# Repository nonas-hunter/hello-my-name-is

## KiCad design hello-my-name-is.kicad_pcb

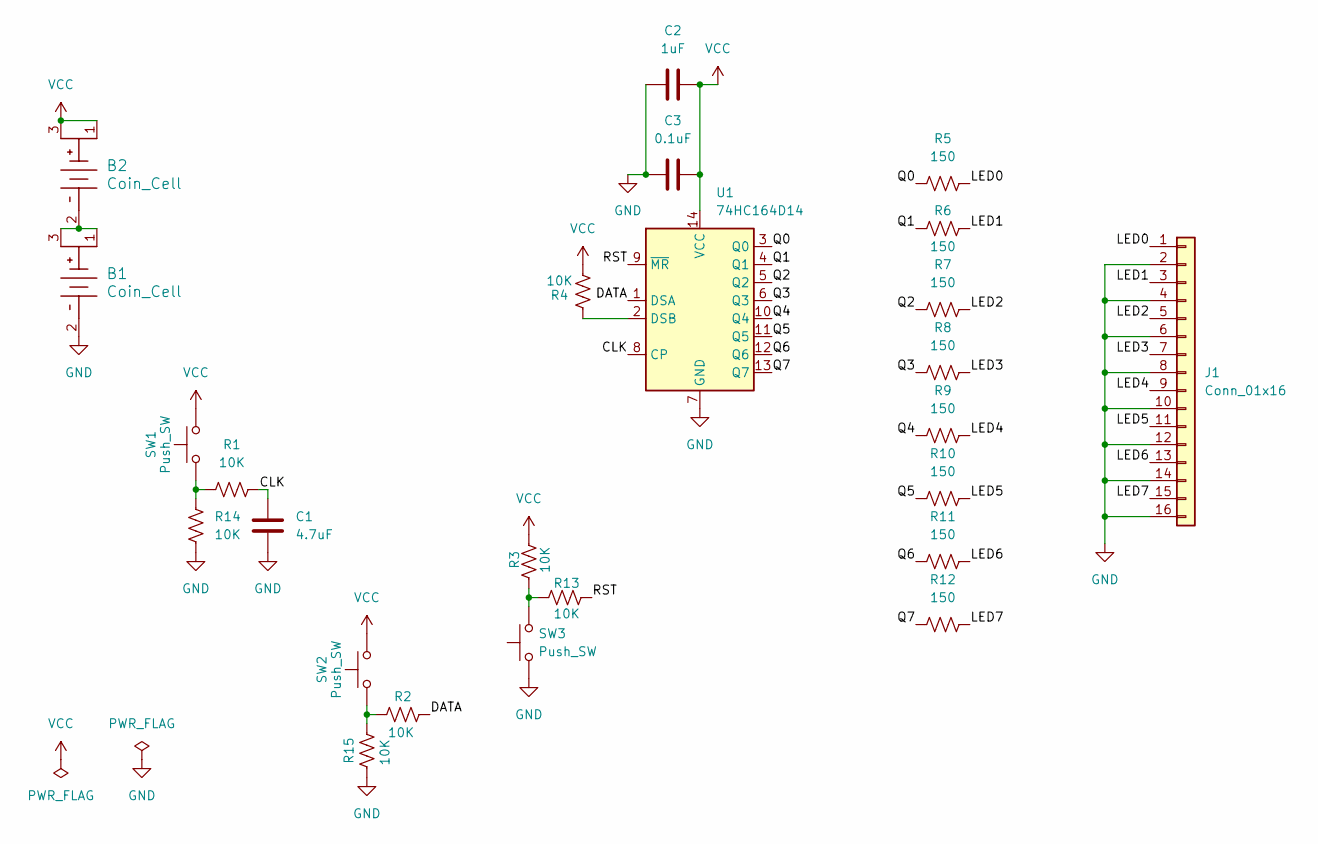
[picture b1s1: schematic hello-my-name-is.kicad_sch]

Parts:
B1, B2: Coin_Cell; BATT_HLDR_LNX; Part Number (DigiKey) BAT-HLD-001-ND
C1: 4.7uF; C_Disc_D8.0mm_W2.5mm_P5.00mm; Part Number (DigiKey) 445-173255-1-ND
C2: 1uF; C_Disc_D8.0mm_W2.5mm_P5.00mm; Part Number (DigiKey) 445-173255-1-ND
C3: 0.1uF; C_Disc_D8.0mm_W2.5mm_P5.00mm; Part Number (DigiKey) BC1084CT-ND
J1: Conn_01x16; PinSocket_1x32_P6.08mm_Vertical
R1, R2, R3, R4, R13, R14, R15: 10K; R_Axial_DIN0207_L6.3mm_D2.5mm_P10.16mm_Horizontal
R5, R6, R7, R8, R9, R10, R11, R12: 150; R_Axial_DIN0207_L6.3mm_D2.5mm_P10.16mm_Horizontal
SW1, SW2, SW3: Push_SW; SW_TH_Tactile_Omron_B3F-10xx; Part Number (DigiKey) SW950-ND
U1: 74HC164D14; DIP-14_W7.62mm; Part Number (DigiKey) 74HC164D14DI-ND

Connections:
/CLK: C1.1, R1.2, U1.8 (CP)
/DATA: R2.2, U1.1 (DSA)
/LED0: J1.1, R5.2
/LED1: J1.3, R6.2
/LED2: J1.5, R7.2
/LED3: J1.7, R8.2
/LED4: J1.9, R9.2
/LED5: J1.11, R10.2
/LED6: J1.13, R11.2
/LED7: J1.15, R12.1
/Q0: R5.1, U1.3 (Q0)
/Q1: R6.1, U1.4 (Q1)
/Q2: R7.1, U1.5 (Q2)
/Q3: R8.1, U1.6 (Q3)
/Q4: R9.1, U1.10 (Q4)
/Q5: R10.1, U1.11 (Q5)
/Q6: R11.1, U1.12 (Q6)
/Q7: R12.2, U1.13 (Q7)
/RST: R13.2, U1.9 (~MR)
GND: B1.2, C1.2, C2.1, C3.2, J1.2, J1.4, J1.6, J1.8, J1.10, J1.12, J1.14, J1.16, R14.1, R15.1, SW3.1, U1.7 (GND)
unnamed: B1.1, B1.3, B2.2
unnamed: R1.1, R14.2, SW1.1
unnamed: R3.1, R13.1, SW3.2
unnamed: R2.1, R15.2, SW2.1
unnamed: R4.2, U1.2 (DSB)
VCC: B2.1, B2.3, C2.2, C3.1, R3.2, R4.1, SW1.2, SW2.2, U1.14 (VCC)

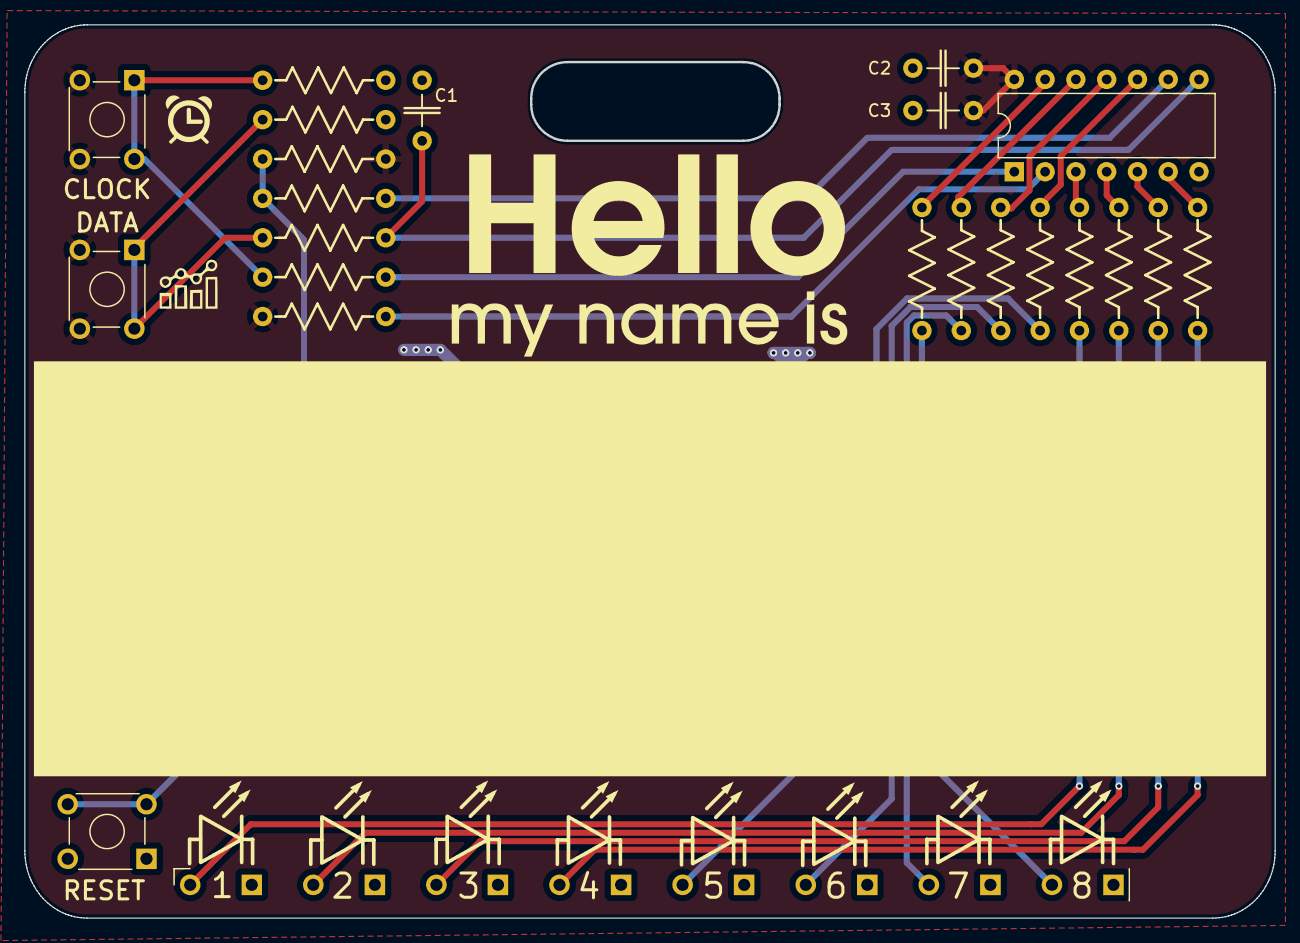
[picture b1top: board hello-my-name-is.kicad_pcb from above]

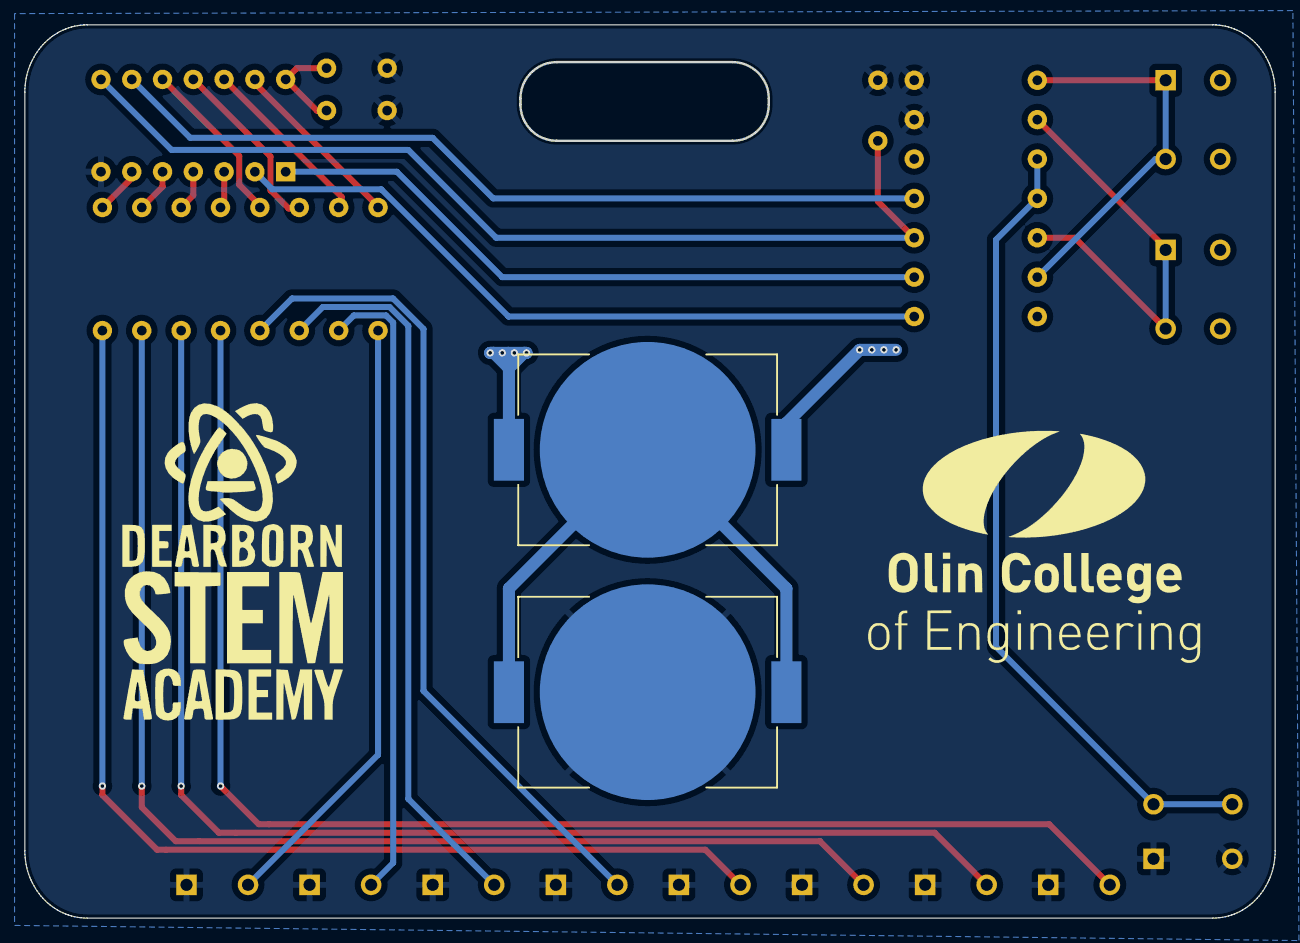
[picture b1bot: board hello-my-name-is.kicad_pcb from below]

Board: 2 copper layers, 103.1 x 73.6 mm, 25 parts (2 on the bottom side), 26 nets.

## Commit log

2024-06-07 Commit first revision of name tag
